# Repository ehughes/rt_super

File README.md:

# RT685 SuperMonkey- Hardware #

This repo has the PCB design data for the SuperMonkey that is based upon the i.MXRT685 in a VFBGA176 package.  This design was created to show a minimal configuration example of the i.MXRT685 using QSPI flash on FlexSPI port A.    Each PCB revision is in its own folder.  I typically always keep copies of all revisions in one repo so I can have access to multiple CCA versions at one time (instead of branches for each PCB/CCA).   Branches are used for development and merged into master when boards are sent out.

The SuperMonkey is in a prototype state.   Use at your own risk.

### Latest Revision - Navigation ###

The revisions is are PCB Rev B1 and PCB Rev C. 

Rev C is a new formfactor with more pins and integrated OCTAL PSRAM

The design files are in Altium v21 format.

### History/Notes

#### PCB REV B:

- 1st official prototype.   Rev A was dispositioned.

#### PCB REV B:

- 1st official prototype.   Rev A was dispositioned.

#### PCB REV B1:

- Minor Fix to the I2C PMIC Interface
- Font Fixes

#### PCB REV C:

- New Form Factor MK-76 PGA
- No Onboard flash.  Octal PSRA<>

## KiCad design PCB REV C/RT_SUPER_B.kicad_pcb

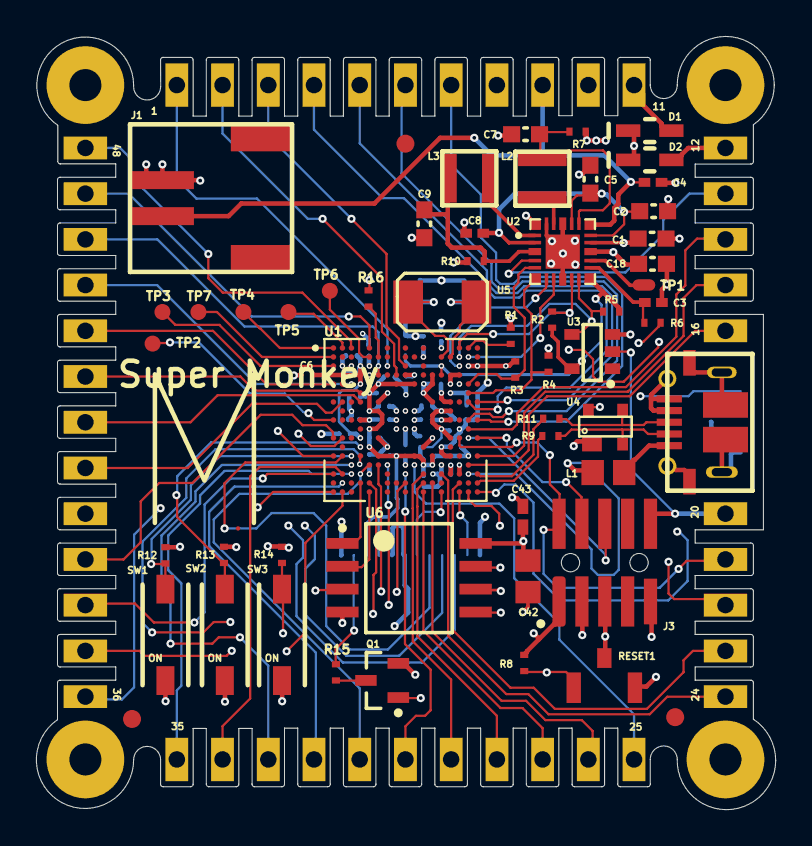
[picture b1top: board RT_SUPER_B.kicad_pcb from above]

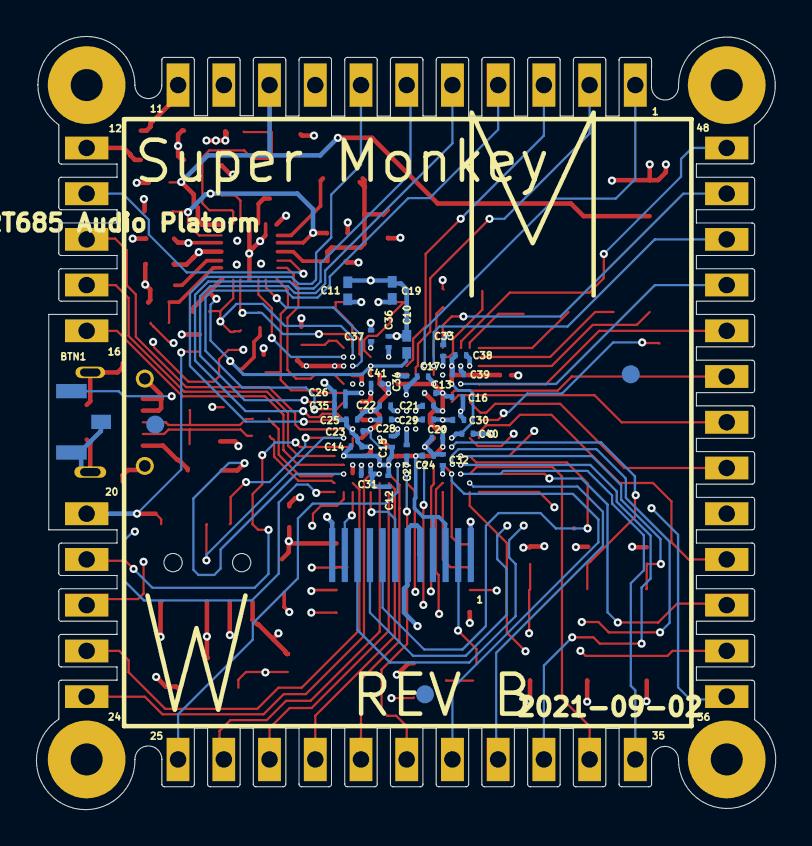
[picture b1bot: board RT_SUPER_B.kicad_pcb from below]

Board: 4 copper layers, 41.1 x 43.0 mm, 138 parts (36 on the bottom side), 95 nets.

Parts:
BTN1: B3U-1100P; OMRON_B3U-1100P
C1, C5, C18: 2.2µF; C0603_0.90MM_MD
C2: 4.7µF; C0603_1.00MM_MD
C3: 0.47µF; C0402_0.55MM_HD
C4, C8, C10: 1µF; C0402_0.55MM_HD
C6, C12, C13, C14, C15, C16, C17, C20, C21, C22, C23, C24, C25, C26, C27, C28, C29, C30, C31, C32, C33, C34, C35, C36, C37, C38, C39, C40, C41: 0.1uF 6v; C0201_PERFECT
C7, C9: 10µF; C0603_0.90MM_MD
C11, C19: 18pF; C0402_0.55MM_HD
C42: 4.7µF; _Users_EliHughes_TZero Research and Development_Altium Reso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
C43: 0.1µF; _Users_EliHughes_TZero Research and Development_Altium Reso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
D1: BAT760-7; _Users_EliHughes_TZero Research and Development_Altium Reso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
D2: BAT760-7; _Users_Eli Hughes_TZero Research and Development_Altium Res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
F1, F2, F3, F4, F5, F6: PCB Fiducial; Fiducial 1mm - 2mm
J1: S2B-PH-SM4-TB(LF)(SN)
J2: 10103594-0001LF
J3: FTSH-105-01-F-DV; FTSH-105-01-F-DV-K-A
L1: CBC2012T4R7M; C0805_1.45MM_MD
L2, L3: 2.2µH 1.5A; _Users_EliHughes_TZero Research and Development_Altium Reso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
P1, P2, P3, P4, P5, P6, P7, P8, P9, P10, P11, P12, P13, P14, P15, P16, P20, P21, P22, P23, P24, P25, P26, P27, P28, P29, P30, P31, P32, P33, P34, P35, P36, P37, P38, P39, P40, P41, P42, P43, P44, P45, P46, P47, P48: CASTELLATED
Q1: ZXMN3A01FTA; SOT-23
R1: 10k; R0402_0.40MM_HD
R2, R5: 20k; _Users_EliHughes_TZero Research and Development_Altium Reso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
R3, R4: 2.2k; _Users_EliHughes_TZero Research and Development_Altium Reso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
R6, R7, R10: 0; R0402_0.40MM_HD
R8, R12, R13, R14: 100k; R0402_0.40MM_HD
R9, R11, R15: 33; R0402_0.40MM_HD
R16: 1k; R0402_0.40MM_HD
RESET1: B3U-1100P; OMRON_B3U-1100P
SW1, SW2, SW3: CHS-01TA
TP1: SMT_TEST; SMT_TP - 25 x 50
TP2, TP3, TP4, TP5, TP6, TP7: SMT_TEST; SMT_TP - 35
U1: MIMXRT685SFVKB; VFBGA176
U2: PCA9420BSAZ; PCA9420
U3: SN74AUC1G07DBVR; SOT23-5
U4: PRTR5V0U2X,215; SOT143B
U5: 24MHz; ABM3
U6: W25Q64JVSIM; SOIC127P830X200-8L
U7: ER-TFT1.54-1

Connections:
+1v8: C6.2, C36.2, C37.2, C38.2, C39.2, C40.2, C41.2, R3.2, R4.2, R10.2, U1.A13, U1.B11, U1.C4, U1.C16, U1.C17, U1.D2, U1.E4, U1.E15, U1.F13, U1.G14, U1.L4, U1.R15
+1v8_AO: C10.2, R2.2, R5.2, U1.C13, U1.D13, U2.12, U3.5
+3v3: C12.2, C13.2, C14.2, C15.2, C16.2, C17.2, C18.2, C20.2, C21.2, C22.2, C23.2, C24.2, C25.2, C42.2, C43.1, J3.1, P10.1, R8.2, R12.2, R13.2, R14.2, U1.E6, U1.E8, U1.E10, U1.F5, U1.H5, U1.H13, U1.H14, U1.K5, U1.K13, U1.L14, U1.M5, U1.N6, U1.N8, U1.N10, U1.N12, U1.N16, U1.P11, U1.P12, U2.15, U6.8, U7.3, U7.4
+5vUSB: D2.1, L1.2, P12.1, U1.R16, U4.4
+VBATT: C4.2, J1.2, P9.1, R6.2, U2.18
+VBATT_BU: C3.2, R6.1, U2.13
+VIN: D1.1, P11.1
ADC0_0: P43.1, U1.F4
ADC0_1: P45.1, U1.E3
ADC0_8: P44.1, U1.E1
BTN: BTN1.2, U1.U17
DEBUG_RX_IN: P42.1, U1.G4
DEBUG_TX_OUT: P41.1, U1.G2
DM_MCU: R9.2, U1.T17
DP_MCU: R11.2, U1.R17
FC2_CLK: P48.1, U1.A3
FC2_SDA: P46.1, U1.D6
FC2_WS: P47.1, U1.A5
FC3_CLK: P1.1, U1.C7
FC3_SDA: P3.1, U1.C9
FC3_WS: P2.1, U1.D8
FC5_RXD: P6.1, U1.J16
FC5_SCK: P4.1, U1.G16
FC5_SSEL0: P7.1, U1.J17
FC5_TXD: P5.1, U1.G17
GND: BTN1.1, BTN1.S, C1.1, C2.2, C3.1, C4.1, C5.2, C6.1, C7.1, C8.2, C9.1, C10.1, C11.1, C12.1, C13.1, C14.1, C15.1, C16.1, C17.1, C18.1, C19.1, C20.1, C21.1, C22.1, C23.1, C24.1, C25.1, C26.1, C27.1, C28.1, C29.1, C30.1, C31.1, C32.1, C33.1, C34.1, C35.1, C36.1, C37.1, C38.1, C39.1, C40.1, C41.1, C42.1, C43.2, J1.1, J2.4, J2.5, J2.MOUNT, J3.3, J3.5, J3.9, P8.1, P40.1, Q1.2, R1.1, RESET1.1, RESET1.S, SW1.1, SW2.1, SW3.1, U1.C2, U1.C3, U1.D5, U1.D12, U1.D15, U1.E12, U1.E14, U1.F7, U1.F11, U1.G6, U1.G12, U1.H8, U1.H9, U1.H10, U1.J8, U1.J10, U1.K8, U1.K9, U1.K10, U1.L6, U1.L12, U1.M7, U1.M11, U1.M13, U1.N14, U1.P13, U2.9, U2.21, U2.23, U2.24, U2.25, U3.3, U4.1, U6.4, U7.1, U7.5, U7.6, U7.12
HS_SPI_MOSI: U1.N1, U7.10
HS_SPI_SCK: U1.L2, U7.9
HS_SPI_SSEL0: U1.N2, U7.8
I3C0_PUR: R16.1, U1.B6
I3C0_SCL: P15.1, U1.N17
I3C0_SDA: P16.1, R16.2, U1.P16
ISP0: R12.1, SW1.2, U1.N3
ISP1: R13.1, SW2.2, U1.M4
ISP2: R14.1, SW3.2, U1.N4
LCD_BL: Q1.1, U1.U16
LCD_CMD_DATA: U1.U13, U7.7
LCD_RST: U1.U15, U7.11
MCLK: P14.1, U1.K16
NetC1_2: C1.2, D1.2, D2.2, U2.16
NetC2_1: C2.1, C5.1, C8.1, U2.2, U2.17, U2.20
NetC7_2: C7.2, L2.2, R7.1, U2.19
NetC9_2: C9.2, L3.2, R10.1, U2.3
NetC11_2: C11.2, U1.B14, U5.2
NetC19_2: C19.2, U1.B13, U5.1
NetJ2_1: J2.1, L1.1
NetJ2_2: J2.2, R9.1, U4.2
NetJ2_3: J2.3, R11.1, U4.3
NetL2_1: L2.1, U2.22
NetL3_1: L3.1, U2.1
NetQ1_3: Q1.3, R15.1
NetR1_2: R1.2, U1.A16
NetR15_2: R15.2, U7.2
NetTP2_1: TP2.1, U1.J1
NetTP3_1: TP3.1, U1.C1
NetTP4_1: TP4.1, U1.A1
NetTP5_1: TP5.1, U1.A2
PDM_CLK01: P38.1, U1.R1
PDM_CLK23: P36.1, U1.U1
PDM_CLK45: P34.1, U1.R2
PDM_CLK67: P32.1, U1.T2
PDM_DATA01: P37.1, U1.U2
PDM_DATA23: P35.1, U1.R3
PDM_DATA45: P33.1, U1.P3
PDM_DATA67: P31.1, U1.P5
PIO0_11: P39.1, U1.L1
PIO1_8: TP6.1, U1.B5
PIO1_9: TP7.1, U1.B1
PMIC_INTB: R2.1, U1.A15, U2.10
PMIC_MODE0: U1.C15, U2.7
PMIC_MODE1: U1.B16, U2.8
PMIC_ON: P13.1, U2.4
PMIC_RESETN: R5.1, U1.B15, U2.11, U3.4
PMIC_SCL: R3.1, U1.E16, U2.5
PMIC_SDA: R4.1, U1.F16, U2.6
QSPI_CS: U1.T4, U6.1
QSPI_D0: U1.T5, U6.5
QSPI_D1: U1.U5, U6.2
QSPI_D2: U1.P6, U6.3
QSPI_D3: U1.P7, U6.7
QSPI_SCK: U1.T9, U6.6
RST_3V3: J3.10, P20.1, R8.1, RESET1.2, U3.2
SD_CLK: P25.1, U1.P10
SD_CMD: P30.1, U1.R9
SD_D0: P29.1, U1.R11
SD_D1: P28.1, U1.T11
SD_D2: P27.1, U1.U11
SD_D3: P26.1, U1.T12
SD_DETECT_N: P24.1, U1.R13
SD_RESET_N: P23.1, U1.T15
SWCLK: J3.4, P22.1, U1.L17
SWIO: J3.2, P21.1, U1.L15
SWO: J3.6, U1.L16
TEMP_SENSE: TP1.1, U2.14
VDD_CORE: C26.2, C27.2, C28.2, C29.2, C30.2, C31.2, C32.2, C33.2, C34.2, C35.2, R7.2, U1.C5, U1.D9, U1.F14, U1.J4, U1.J14, U1.P9, U1.R5, U1.R14

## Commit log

2021-10-16 1st add
2021-10-16 fixed typo on QSPI flash memory part number
2021-10-16 fixed pin numbers on schematic for better readability
2022-02-09 adding in KiCad Import
2022-12-07 added schematic bug notes
2022-12-27 working on C....
2022-12-27 1st pass route
2022-12-28 dev update
2023-01-03 reworking C
2023-01-05 route update
2023-01-05 route up
2023-01-08 rev C for budgetary quote
2023-04-17 Test123
2023-04-17 test
2023-11-06 Seeding...
2023-11-06 cleaning up...
2023-11-06 Seeding
2023-11-16 seeding the host
2023-11-17 ev update
2023-11-18 reorg
2023-11-19 outjob updates
2023-11-19 working on outjob
2023-11-19 outjob update
2023-11-28 updated SM module IO. Bad PIO number on ADC0_3
2023-11-29 Adding note that FC5 connection to LCD is incorrect. TXD is SPI MISO, not MOSI
2024-08-20 starting on MK84
2024-08-21 board outline define
